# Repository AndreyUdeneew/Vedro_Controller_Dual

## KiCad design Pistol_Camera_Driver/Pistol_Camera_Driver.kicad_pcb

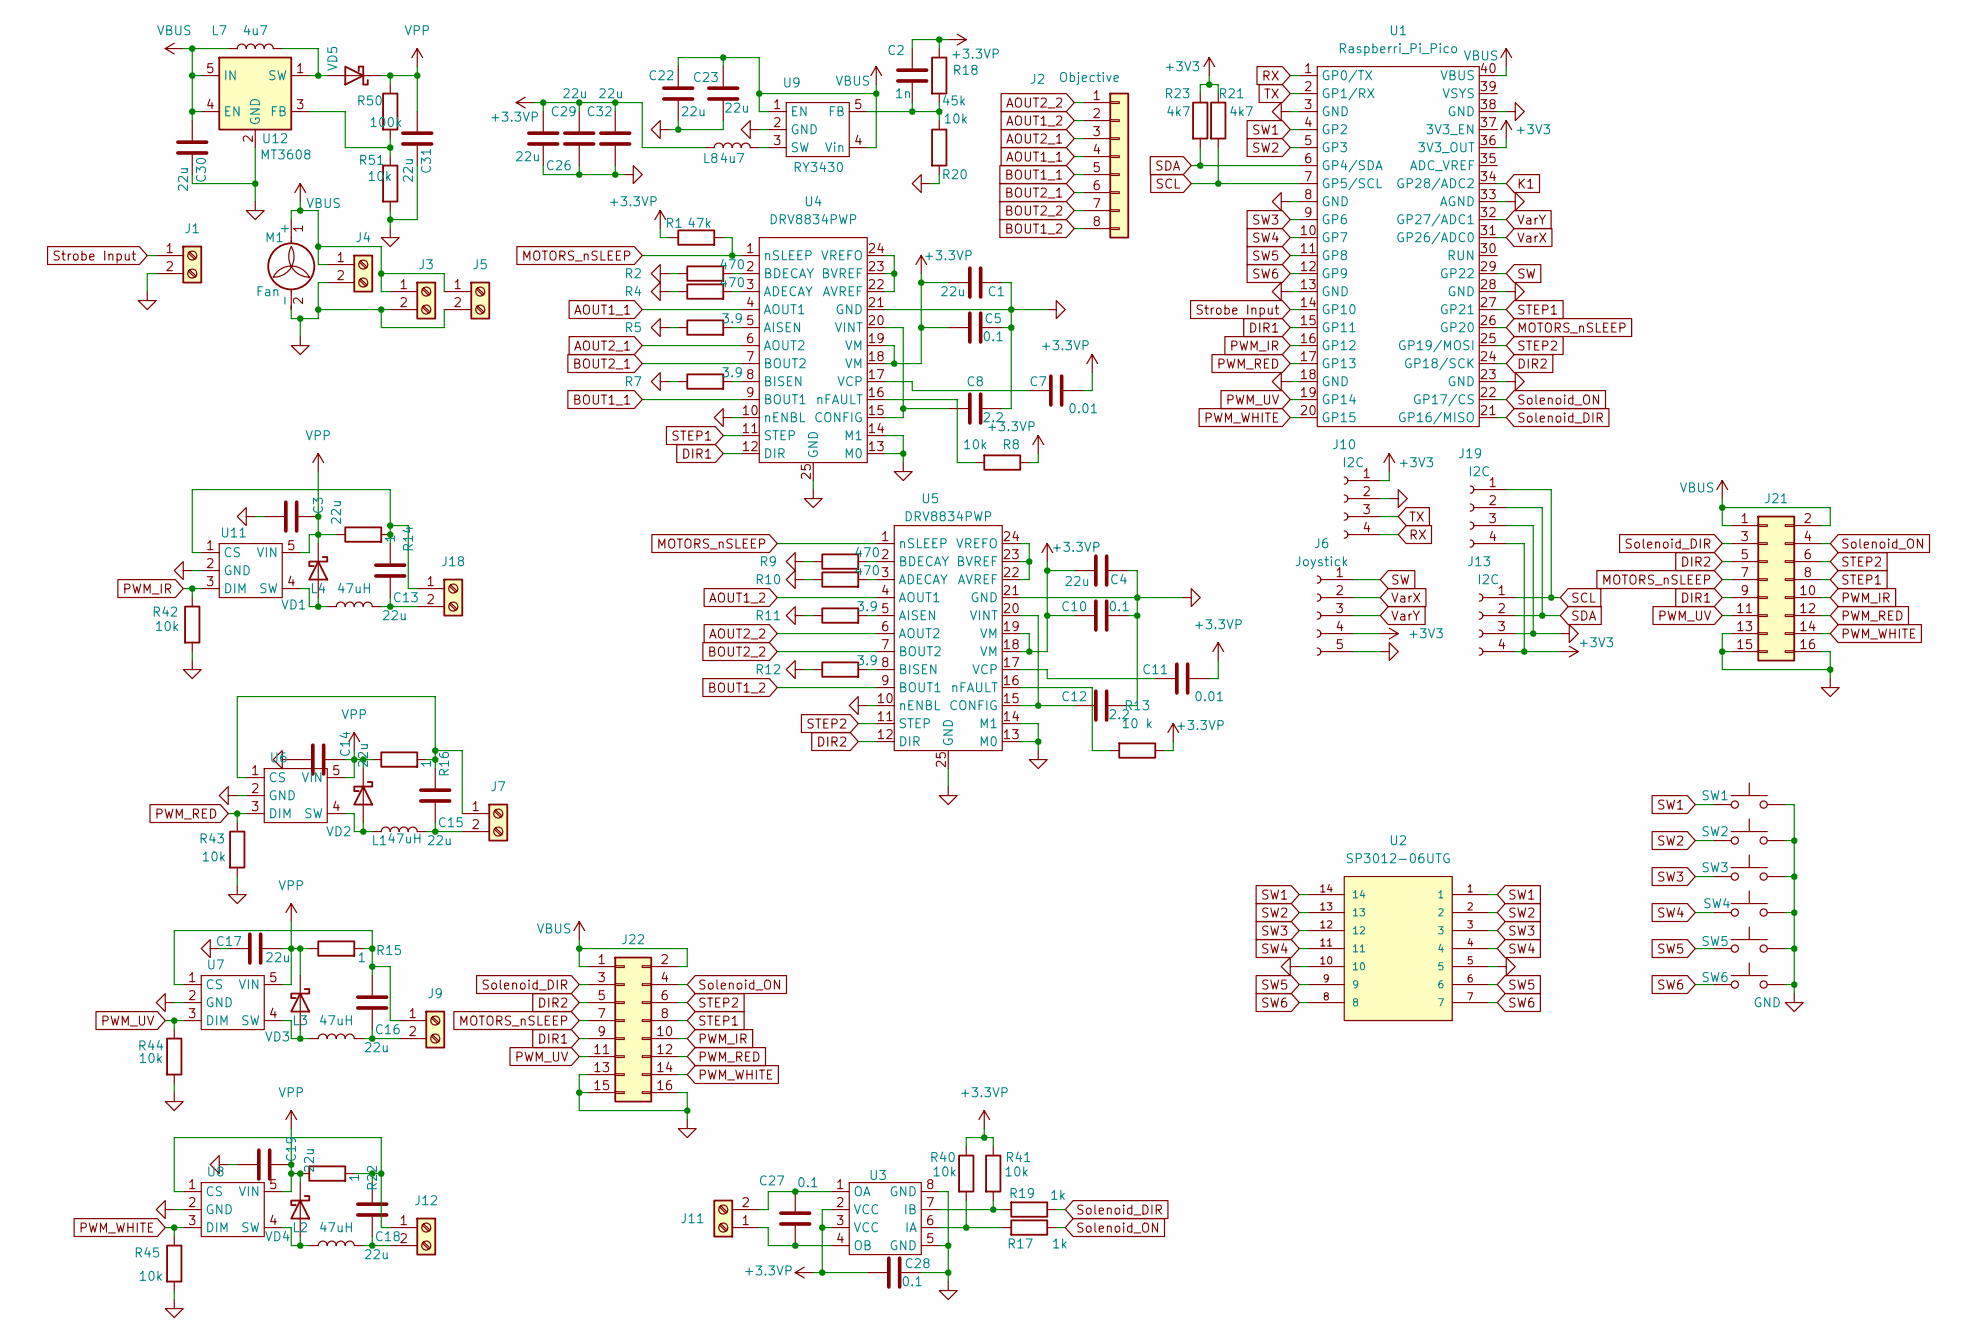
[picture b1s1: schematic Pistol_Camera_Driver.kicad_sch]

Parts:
C1, C3, C4, C13, C14, C15, C16, C17, C18, C19, C22, C23, C26, C29, C32: 22u; C_0805_2012Metric_Pad1.18x1.45mm_HandSolder
C2: 1n; C_0603_1608Metric_Pad1.08x0.95mm_HandSolder
C5, C10, C27, C28: 0.1; C_0603_1608Metric_Pad1.08x0.95mm_HandSolder
C7, C11: 0.01; C_0603_1608Metric_Pad1.08x0.95mm_HandSolder
C8, C12: 2.2; C_0603_1608Metric_Pad1.08x0.95mm_HandSolder
C30, C31: 22u; C_0603_1608Metric_Pad1.08x0.95mm_HandSolder
J1, J3, J4, J5, J7, J9, J12, J18: Screw_Terminal_01x02; JST_XH_B2B-XH-A_1x02_P2.50mm_Vertical
J2: Objective; PinSocket_1x08_P1.27mm_Vertical
J6: Joystick; JST_XH_B5B-XH-A_1x05_P2.50mm_Vertical
J10: I2C; PinSocket_1x04_P2.54mm_Vertical
J11: Screw_Terminal_01x02; PinSocket_1x02_P1.27mm_Vertical
J13, J19: I2C; JST_XH_B4B-XH-A_1x04_P2.50mm_Vertical
J21, J22: Conn_02x08_Odd_Even; IDC-Header_2x08_P2.54mm_Vertical
L1, L2, L3, L4: 47uH; L_APV_ANR5045
L7, L8: 4u7; L_Chilisin_BMRx00040412
M1: Fan
R1: 47k; R_0603_1608Metric_Pad0.98x0.95mm_HandSolder
R2, R4, R9, R10: 470; R_0603_1608Metric_Pad0.98x0.95mm_HandSolder
R5, R7, R11, R12: 3.9; R_0603_1608Metric_Pad0.98x0.95mm_HandSolder
R8, R20, R40, R41, R42, R43, R44, R45, R51: 10k; R_0603_1608Metric_Pad0.98x0.95mm_HandSolder
R13: 10 k; R_0603_1608Metric_Pad0.98x0.95mm_HandSolder
R14, R15, R16, R22: 1; R_0603_1608Metric_Pad0.98x0.95mm_HandSolder
R17, R19: 1k; R_0603_1608Metric_Pad0.98x0.95mm_HandSolder
R18: 45k; R_0603_1608Metric_Pad0.98x0.95mm_HandSolder
R21, R23: 4k7; R_0603_1608Metric_Pad0.98x0.95mm_HandSolder
R50: 100k; R_0603_1608Metric_Pad0.98x0.95mm_HandSolder
SW1, SW2, SW3, SW4, SW5, SW6: SW_Push; SW_PUSH_6mm
U1: Raspberri_Pi_Pico; RP2040-LCD-0.96
U2: SP3012-06UTG; DFN-14_1.35x3.5mm_P0.5mm; PARTREV 02/23/17
U3: SOIC-8_3.9x4.9mm_P1.27mm
U4, U5: DRV8834PWP
U6, U7, U8, U11: SOT-89-5
U9: RY3430; SOT-23-5
U12: MT3608; SOT-23-6
VD1, VD2, VD3, VD4, VD5: CDBA3100-HF; D_SOD-123

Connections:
+3.3VP: C1.1, C2.1, C4.1, C5.2, C7.2, C10.1, C11.2, C26.1, C28.2, C29.2, C32.2, L8.1, R1.1, R8.1, R13.1, R18.1, R40.1, R41.1, U3.2 (VCC), U3.3 (VCC), U4.18 (VM), U4.19 (VM), U5.18 (VM), U5.19 (VM)
+3V3: J6.4, J10.1, J13.4, J19.4, R21.1, R23.1, U1.36 (3V3_OUT)
AOUT1_1: J2.4, U4.4 (AOUT1)
AOUT1_2: J2.2, U5.4 (AOUT1)
AOUT2_1: J2.3, U4.6 (AOUT2)
AOUT2_2: J2.1, U5.6 (AOUT2)
BOUT1_1: J2.5, U4.9 (BOUT1)
BOUT1_2: J2.8, U5.9 (BOUT1)
BOUT2_1: J2.6, U4.7 (BOUT2)
BOUT2_2: J2.7, U5.7 (BOUT2)
DIR1: J21.9, J22.9, U1.15 (GP11), U4.12 (DIR)
DIR2: J21.5, J22.5, U1.24 (GP18/SCK), U5.12 (DIR)
GND: C1.2, C3.1, C4.2, C5.1, C8.2, C10.2, C12.2, C14.1, C17.1, C19.1, C22.2, C23.1, C26.2, C28.1, C29.1, C30.2, C31.2, C32.1, J1.2, J3.2, J4.2, J5.2, J6.5, J10.2, J13.3, J19.3, J21.13, J21.15, J21.16, J22.13, J22.15, J22.16, M1.2 (-), R2.1, R4.1, R5.1, R7.1, R9.1, R10.1, R11.1, R12.1, R20.2, R42.2, R43.2, R44.2, R45.2, R51.2, SW1.2, SW2.2, SW3.2, SW4.2, SW5.2, SW6.2, U1.3 (GND), U1.8 (GND), U1.13 (GND), U1.18 (GND), U1.23 (GND), U1.28 (GND), U1.33 (AGND), U1.38 (GND), U2.5, U2.10, U3.5 (GND), U3.8 (GND), U4.10 (nENBL), U4.13 (M0), U4.14 (M1), U4.21 (GND), U4.25 (GND), U5.10 (nENBL), U5.13 (M0), U5.14 (M1), U5.21 (GND), U5.25 (GND), U6.2 (GND), U7.2 (GND), U8.2 (GND), U9.2 (GND), U11.2 (GND), U12.2 (GND)
K1: U1.34 (GP28/ADC2)
MOTORS_nSLEEP: J21.7, J22.7, R1.2, U1.26 (GP20), U4.1 (nSLEEP), U5.1 (nSLEEP)
unnamed: C15.1, J7.1, R16.2, U6.1 (CS)
unnamed: C15.2, J7.2, L1.2
unnamed: C16.1, J9.1, R15.2, U7.1 (CS)
unnamed: C16.2, J9.2, L3.2
unnamed: C27.2, J11.1, U3.4 (OB)
unnamed: C27.1, J11.2, U3.1 (OA)
unnamed: C18.1, J12.1, R22.2, U8.1 (CS)
unnamed: C18.2, J12.2, L2.2
unnamed: C13.1, J18.1, R14.2, U11.1 (CS)
unnamed: C13.2, J18.2, L4.2
unnamed: R17.2, R40.2, U3.6 (IA)
unnamed: R19.2, R41.2, U3.7 (IB)
unnamed: R4.2, U4.3 (ADECAY)
unnamed: R5.2, U4.5 (AISEN)
unnamed: U4.22 (AVREF), U4.23 (BVREF), U4.24 (VREFO)
unnamed: R2.2, U4.2 (BDECAY)
unnamed: R7.2, U4.8 (BISEN)
unnamed: C8.1, U4.15 (CONFIG), U4.20 (VINT)
unnamed: C7.1, U4.17 (VCP)
unnamed: R8.2, U4.16 (nFAULT)
unnamed: R10.2, U5.3 (ADECAY)
unnamed: R11.2, U5.5 (AISEN)
unnamed: U5.22 (AVREF), U5.23 (BVREF), U5.24 (VREFO)
unnamed: R9.2, U5.2 (BDECAY)
unnamed: R12.2, U5.8 (BISEN)
unnamed: C12.1, U5.15 (CONFIG), U5.20 (VINT)
unnamed: C11.1, U5.17 (VCP)
unnamed: R13.2, U5.16 (nFAULT)
unnamed: L1.1, U6.4 (SW), VD2.2 (A)
unnamed: L3.1, U7.4 (SW), VD3.2 (A)
unnamed: L2.1, U8.4 (SW), VD4.2 (A)
unnamed: C2.2, R18.2, R20.1, U9.5 (FB)
unnamed: L8.2, U9.3 (SW)
unnamed: L4.1, U11.4 (SW), VD1.2 (A)
unnamed: R50.2, R51.1, U12.3 (FB)
unnamed: L7.2, U12.1 (SW), VD5.2 (A)
PWM_IR: J21.10, J22.10, R42.1, U1.16 (GP12), U11.3 (DIM)
PWM_RED: J21.12, J22.12, R43.1, U1.17 (GP13), U6.3 (DIM)
PWM_UV: J21.11, J22.11, R44.1, U1.19 (GP14), U7.3 (DIM)
PWM_WHITE: J21.14, J22.14, R45.1, U1.20 (GP15), U8.3 (DIM)
RX: J10.4, U1.1 (GP0/TX)
SCL: J13.1, J19.1, R21.2, U1.7 (GP5/SCL)
SDA: J13.2, J19.2, R23.2, U1.6 (GP4/SDA)
STEP1: J21.8, J22.8, U1.27 (GP21), U4.11 (STEP)
STEP2: J21.6, J22.6, U1.25 (GP19/MOSI), U5.11 (STEP)
SW: J6.1, U1.29 (GP22)
SW1: SW1.1, U1.4 (GP2), U2.1, U2.14
SW2: SW2.1, U1.5 (GP3), U2.2, U2.13
SW3: SW3.1, U1.9 (GP6), U2.3, U2.12
SW4: SW4.1, U1.10 (GP7), U2.4, U2.11
SW5: SW5.1, U1.11 (GP8), U2.6, U2.9
SW6: SW6.1, U1.12 (GP9), U2.7, U2.8
Solenoid_DIR: J21.3, J22.3, R19.1, U1.21 (GP16/MISO)
Solenoid_ON: J21.4, J22.4, R17.1, U1.22 (GP17/CS)
Strobe Input: J1.1, U1.14 (GP10)
TX: J10.3, U1.2 (GP1/RX)
VBUS: C22.1, C23.2, C30.1, J3.1, J4.1, J5.1, J21.1, J21.2, J22.1, J22.2, L7.1, M1.1 (+), U1.40 (VBUS), U9.1 (EN), U9.4 (Vin), U12.4 (EN), U12.5 (IN)
VPP: C3.2, C14.2, C17.2, C19.2, C31.1, R14.1, R15.1, R16.1, R22.1, R50.1, U6.5 (VIN), U7.5 (VIN), U8.5 (VIN), U11.5 (VIN), VD1.1 (K), VD2.1 (K), VD3.1 (K), VD4.1 (K), VD5.1 (K)
VarX: J6.2, U1.31 (GP26/ADC0)
VarY: J6.3, U1.32 (GP27/ADC1)

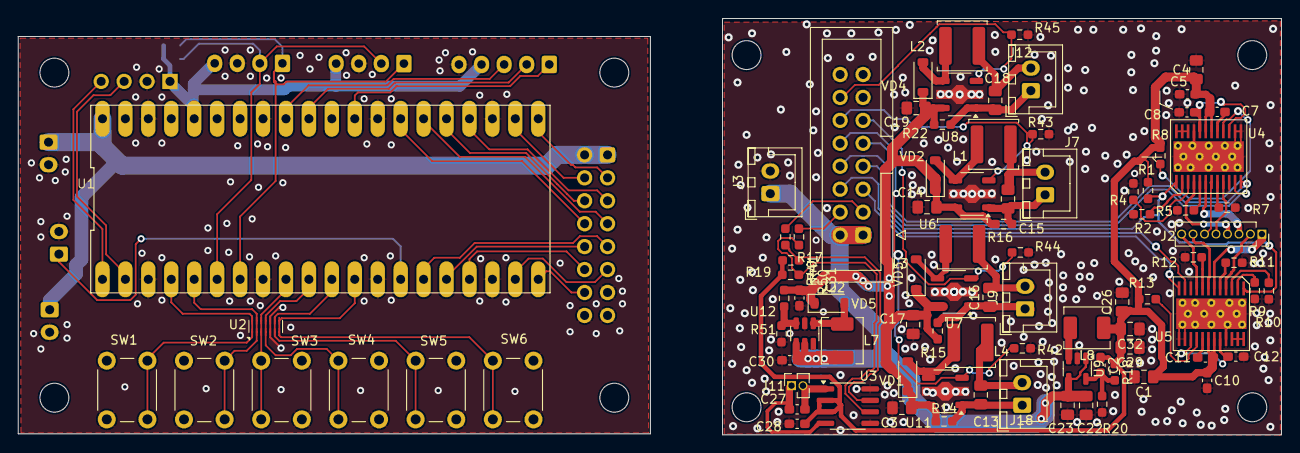
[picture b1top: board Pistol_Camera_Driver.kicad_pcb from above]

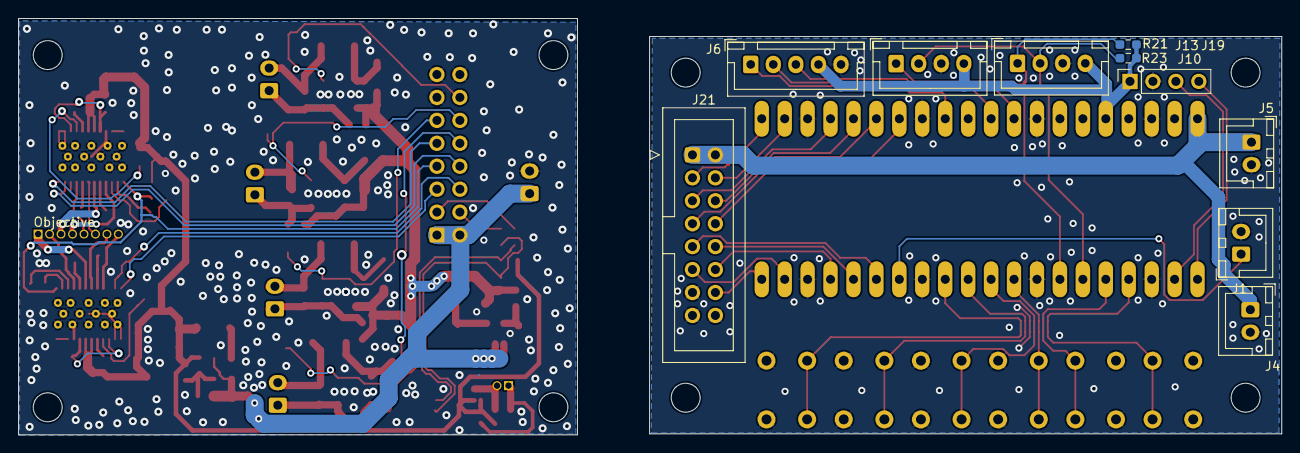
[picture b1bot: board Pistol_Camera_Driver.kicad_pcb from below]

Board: 2 copper layers, 61.9 x 46.1 mm, 99 parts (10 on the bottom side), 74 nets.

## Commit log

2025-02-15 v0.1 Draft routing & DRC completed
2025-02-15 v0.2 Backup *.zip was created
2025-04-22 some test
